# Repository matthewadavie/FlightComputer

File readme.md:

# Flight Computer
This is a fun little project for a drone. Main goals are as below:
 - Powered by a LiPo battery (3S or 4S)
 - USB C for comms to uC (after flight?)
 - IMU, Magnetometer & GPS (because why not), barometer
 - Potentially BLDC motor control? Maybe a stretch goal but we shall see

 ## Parts List:
 - STM32 (uC)
 - U Blox SAM-M10Q (GPS)
 - Bosch Sensortec BMI088 (IMU, may change but I want to try the cool fancy new stuff)
 - Bosch Sensortec BMP390 (Barometer)

 ## Requirements
 - uC voltage: 3.3V
 - Comms: I2C

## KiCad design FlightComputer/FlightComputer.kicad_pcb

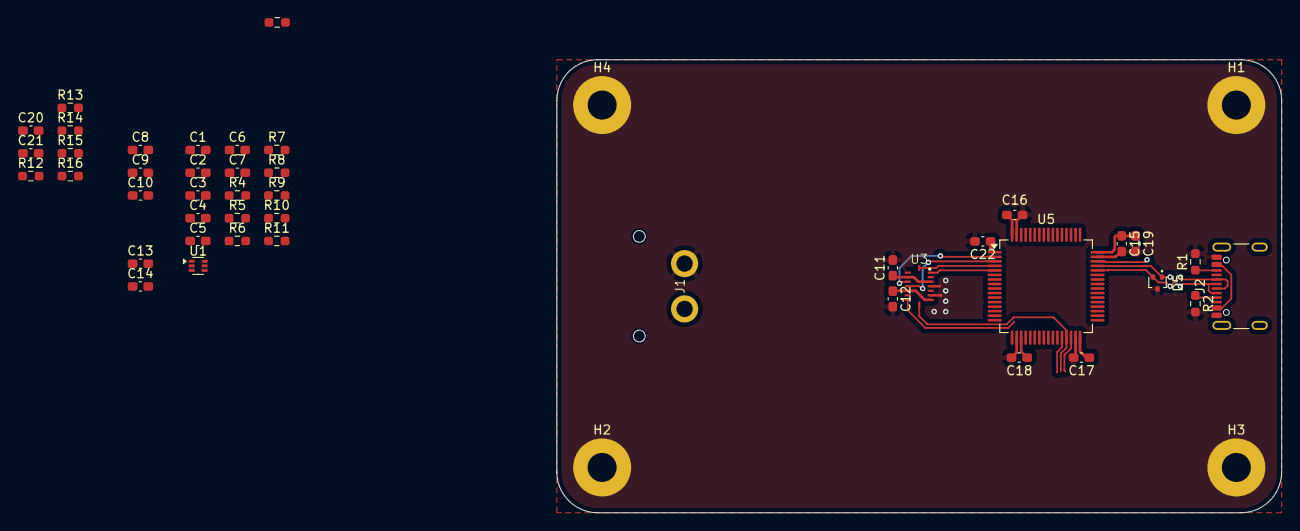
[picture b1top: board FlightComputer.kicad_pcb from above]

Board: 4 copper layers, 80.0 x 50.0 mm, 48 parts (0 on the bottom side), 25 nets.

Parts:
C1, C4, C6, C8, C9, C10, C11, C12, C13, C14, C15, C16, C17, C18, C21, C22: 100n; C_0603_1608Metric_Pad1.08x0.95mm_HandSolder
C2, C3: 22uF; C_0603_1608Metric_Pad1.08x0.95mm_HandSolder
C5, C19: 10u; C_0603_1608Metric_Pad1.08x0.95mm_HandSolder
C7: 10n; C_0603_1608Metric_Pad1.08x0.95mm_HandSolder
C20: 1u; C_0603_1608Metric_Pad1.08x0.95mm_HandSolder
D5: RCLAMP0582B; SOT-416
H1, H2, H3, H4: MountingHole_Pad; MountingHole_3.2mm_M3_Pad
J1: Conn_01x02_Pin; XT60_Right_Angle
J2: USB C Plug (USB 2); USB_C_Receptacle_GCT_USB4105-xx-A_16P_TopMnt_Horizontal
R1, R2, R9: 5.1k; R_0603_1608Metric_Pad0.98x0.95mm_HandSolder
R3: 1M; R_0603_1608Metric_Pad0.98x0.95mm_HandSolder
R4: 110k; R_0603_1608Metric_Pad0.98x0.95mm_HandSolder
R5: 11k; R_0603_1608Metric_Pad0.98x0.95mm_HandSolder
R6: 135k; R_0603_1608Metric_Pad0.98x0.95mm_HandSolder
R7: 30k; R_0603_1608Metric_Pad0.98x0.95mm_HandSolder
R8: 24k; R_0603_1608Metric_Pad0.98x0.95mm_HandSolder
R10, R11: 1k; R_0603_1608Metric_Pad0.98x0.95mm_HandSolder
R12, R13, R14, R15, R16: 10k; R_0603_1608Metric_Pad0.98x0.95mm_HandSolder
U1: TPS562202; SOT-563
U3: BMI088
U5: STM32F103RGTx; LQFP-64_10x10mm_P0.5mm

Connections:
+3V3: C2.1, C3.1, C8.1, C9.1, C10.1, C11.1, C12.1, C13.1, C14.1, C15.1, C16.1, C17.1, C18.1, C19.1, C22.1, R6.1, R14.2, R15.2, R16.2, U3.3 (VDD), U3.7 (PS), U3.11 (VDDIO), U3.14 (CSB1), U5.1 (VBAT), U5.19 (VDD), U5.32 (VDD), U5.48 (VDD), U5.64 (VDD)
/IO/USB_CC1: J2.A5 (CC1), R2.1
/IO/USB_CC2: J2.B5 (CC2), R1.1
/IO/dIO_USB_DN: D5.1 (K1), J2.A7 (D-), J2.B7 (D-), U5.45 (PA12)
/IO/dIO_USB_DP: D5.2 (K2), J2.A6 (D+), J2.B6 (D+), U5.44 (PA11)
/Microcontroller/SCL: R14.1, U3.8 (SCL), U5.29 (PB10)
/Microcontroller/SDA: R15.1, U3.9 (SDA), U5.30 (PB11)
/Microcontroller/dIO_INT1_ACCEL: U3.16 (INT1), U5.4 (PC15)
/Microcontroller/dIO_INT1_GYRO: U3.12 (INT3), U5.3 (PC14)
/Microcontroller/dIO_INT2_ACCEL: U3.1 (INT2), U5.5 (PD0)
/Microcontroller/dIO_INT2_GYRO: U3.13 (INT4), U5.2 (PC13)
/Microcontroller/dI_BOOT0: R12.2, U5.60 (BOOT0)
/Microcontroller/dI_BOOT1: R13.2, U5.28 (PB2)
/Power&Battery/EN: R4.2, R5.1, U1.5 (EN)
/Power&Battery/VBST: C4.1, U1.4 (VBST)
/Power&Battery/VFB: R6.2, R7.1, U1.6 (VFB)
/Power&Battery/VIN: C5.1, C6.1, R4.1, U1.1 (VIN)
/Power&Battery/VSW: C4.2, U1.2 (SW)
/Power&Battery/aIN_VBAT: C7.1, R8.2, R9.1
GND: C1.2, C2.2, C3.2, C5.2, C6.2, C7.2, C8.2, C9.2, C10.2, C11.2, C12.2, C13.2, C14.2, C15.2, C16.2, C17.2, C18.2, C19.2, C20.2, C21.2, C22.2, D5.3 (A), H1.1, H2.1, H3.1, H4.1, J1.2, J2.A1 (GND), J2.A12 (GND), J2.B1 (GND), J2.B12 (GND), R1.2, R2.2, R3.2, R5.2, R7.2, R9.2, U1.3 (GND), U3.4 (GNDA), U3.6 (GNDIO), U3.10 (SDO2), U3.15 (SDO1), U5.12 (VSSA), U5.18 (VSS), U5.31 (VSS), U5.47 (VSS), U5.63 (VSS)
unnamed: J2.S1 (SHIELD), R3.1
unnamed: R16.1, U5.7 (NRST)
VBATT: C1.1, J1.1, R8.1, R10.1
VBUS: J2.A4 (VBUS), J2.A9 (VBUS), J2.B4 (VBUS), J2.B9 (VBUS)
VDDA: C20.1, C21.1, U5.13 (VDDA)

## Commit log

2026-01-18 Adding 3.3V regulator, usb c connector, battery connector and calculations sheet
2026-01-18 Updating calculations, sensors page and adding micro page
2026-01-26 Various updates
